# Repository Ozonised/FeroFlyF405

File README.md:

# FeroFlyF405

FeroFlyF405 is an opensource flight controller based on STM32F405 and runs the open source flight controller firmware, [INAV](https://github.com/iNavFlight/inav).

FeroFlyF405 is designed to be an open hardware platform that enthusiasts and developers can study, modify, build, and use in their own projects.

For those interested in the design process, watch the [YouTube](https://youtu.be/mWAzVRxgooY) video.

## Features

* **Microcontroller:** STM32F405
* **IMU:** LSM6DSL 6-axis accelerometer and gyroscope
* **Barometer:** DPS368
* **Firmware:** INAV
* **Motor outputs:** 12 timer-based output channels
* **CAN bus:** For compatible peripherals
* **I2C:** External sensor and peripheral connectivity
* **UARTs:** 3 serial ports
* **PINIO:** 2 programmable GPIO outputs
* **Current sensing:** Dedicated input for an external current sensor

## Sponsor

A special thanks to **[NextPCB](https://www.nextpcb.com/?code=ozonised)** for sponsoring the FeroFlyF405 project and supporting the development of this open-source flight controller.

Their support helped bring the custom PCB design from the screen to the physical board.

Get high quality PCBs for your project at an affordable rate from **[NextPCB](https://www.nextpcb.com/)**.

## Download
Grab the gerbers and kicad file for the latest stable version from the **[release](https://github.com/Ozonised/FeroFlyF405/releases)** tab.

## Connectivity

| Interface      | Quantity | Purpose                                             |
| -------------- | -------: | --------------------------------------------------- |
| Motor outputs  |       12 | ESCs and other compatible timer-based outputs       |
| CAN bus        |        1 | Compatible CAN peripherals                          |
| I2C            |        1 | External sensors and peripherals                    |
| UART           |        3 | Receivers, GPS, telemetry, and other serial devices |
| PINIO          |        2 | User-configurable GPIO outputs                      |
| Current sensor |        1 | External current-sensing module                     |

> **Note:** Motor output capabilities depend on timer allocation, DMA availability, and firmware configuration. Not all outputs necessarily support every ESC protocol.

## Connectors and Pinout

FeroFlyF405 follows the **Pixhawk connector and pinout standard** for its applicable peripheral interfaces and uses **JST-GH series connectors**.

The PINIO and current-sensor connectors are exceptions to this convention.

## Firmware

FeroFlyF405 runs [INAV](https://github.com/iNavFlight/inav), an open-source flight control firmware for multirotor, fixed-wing, and other UAV platforms.

FeroFlyF405 uses a board-specific INAV target to configure its MCU pins, sensors, timers, communication interfaces, and other hardware resources.

Useful links:
* [FeroFlyF405 Target & Binary](https://github.com/Ozonised/FeroFlyF405-INAV-files)
* [INAV source code](https://github.com/iNavFlight/inav)
* [INAV documentation](https://inavflight.github.io/)

## 3D-Printed Enclosure

The FeroFlyF405 enclosure consists of three 3D-printable parts:

* **Enclosure Top** (`FeroFlyF405 Enclosure-Top.stl`) — Upper section of the enclosure.
* **Enclosure Bottom** (`FeroFlyF405 Enclosure-Bottom.stl`) — Lower section of the enclosure.
* **LED Cap** (`FeroFlyF405 Enclosure-Led Cap.stl`) — Cover for the status and power LEDs, designed to be printed using translucent filament to allow the LED light to pass through.

### Printing Recommendations

* **Top and Bottom:** PETG filament is recommended for durability and heat resistance.
* **LED Cap:** Use translucent filament for better LED visibility.
* **Fasteners:** The enclosure uses M3 screws and threaded inserts.

The STL files are provided so you can print and assemble the enclosure yourself.

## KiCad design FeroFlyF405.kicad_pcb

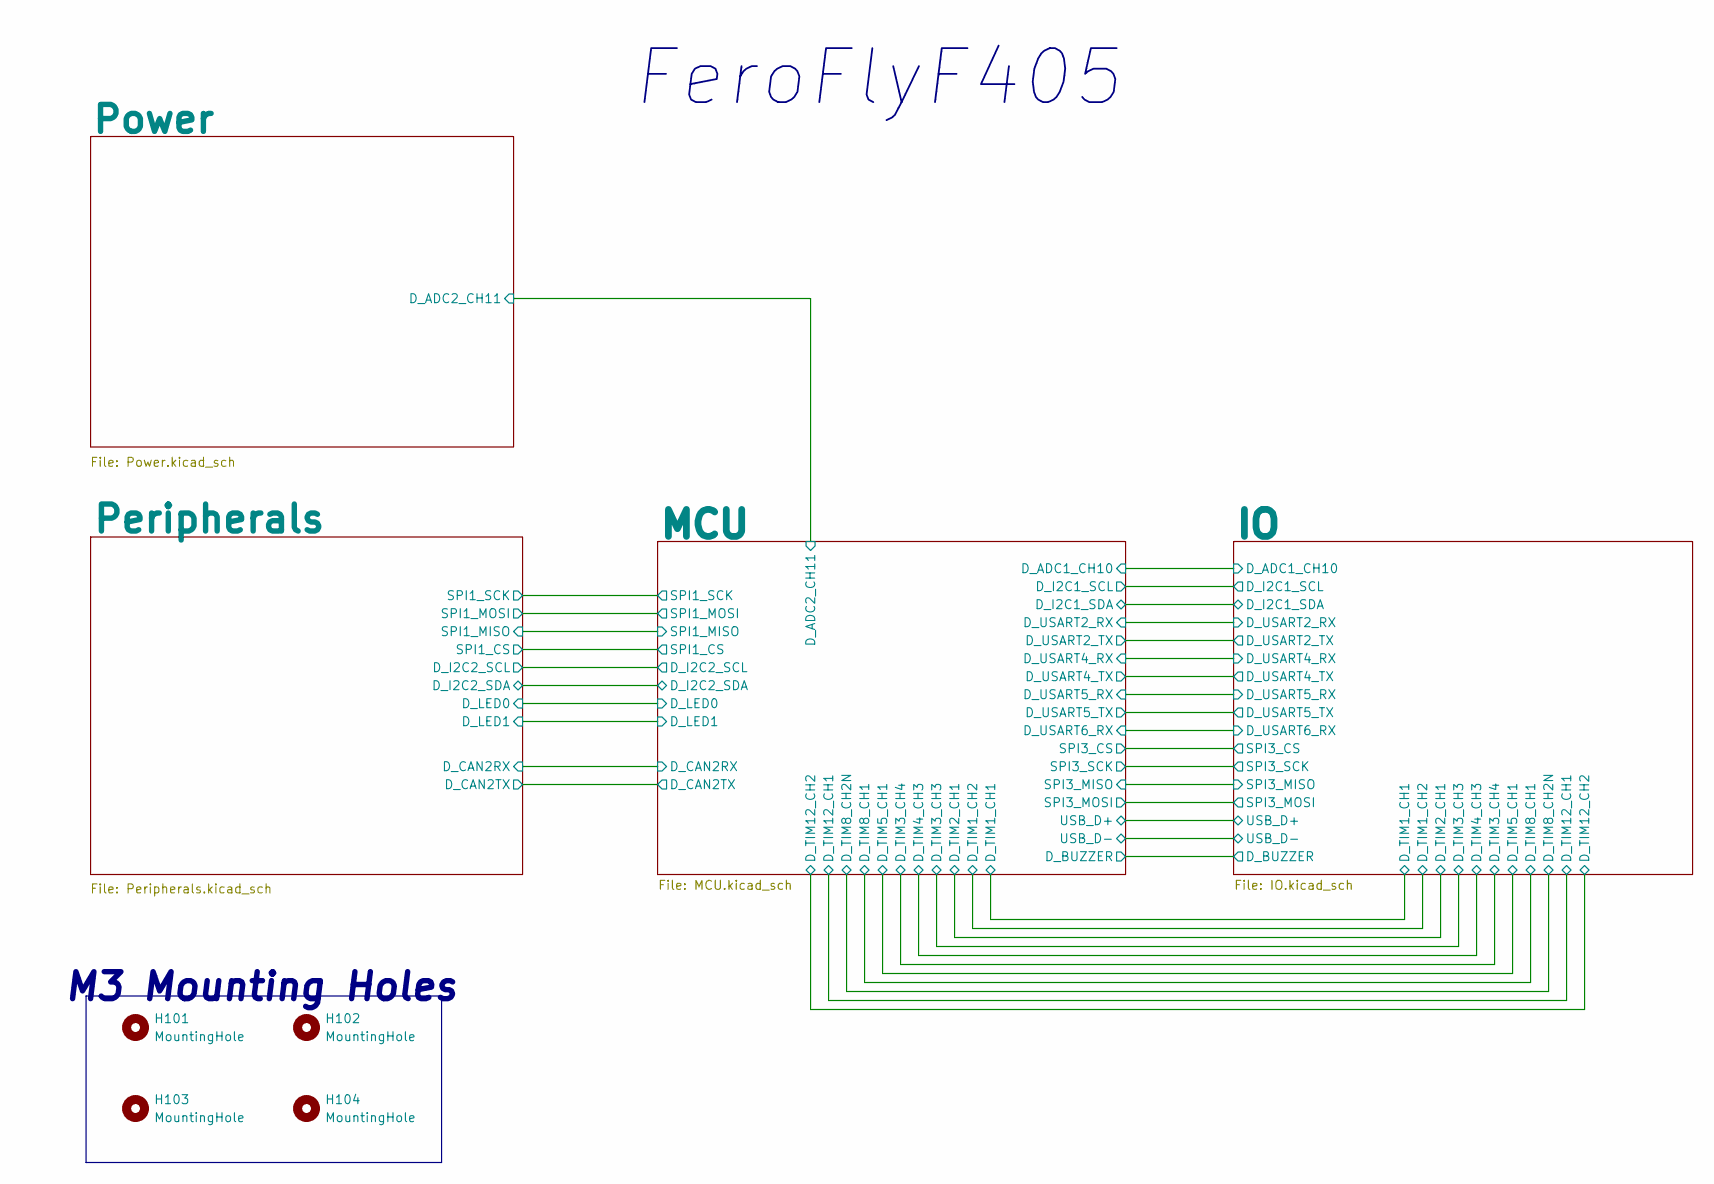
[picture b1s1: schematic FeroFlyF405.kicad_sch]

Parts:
H101, H102, H103, H104: MountingHole; MountingHole_2.2mm_M2

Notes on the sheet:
M3 Mounting Holes
FeroFlyF405

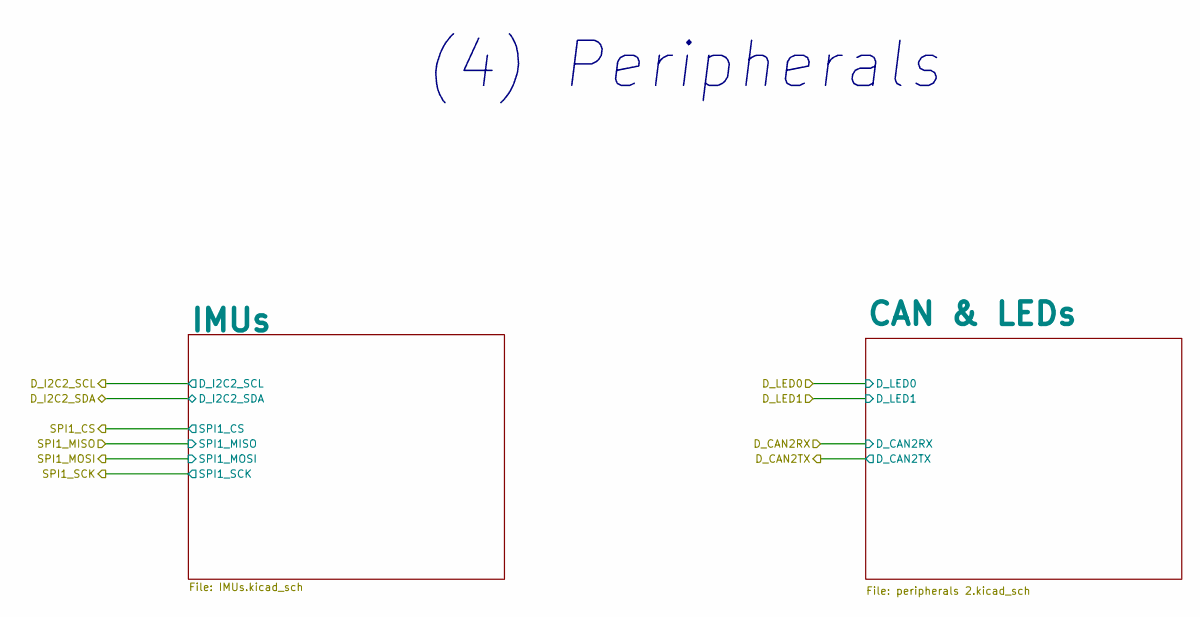
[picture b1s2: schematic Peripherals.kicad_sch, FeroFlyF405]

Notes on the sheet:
(4) Peripherals

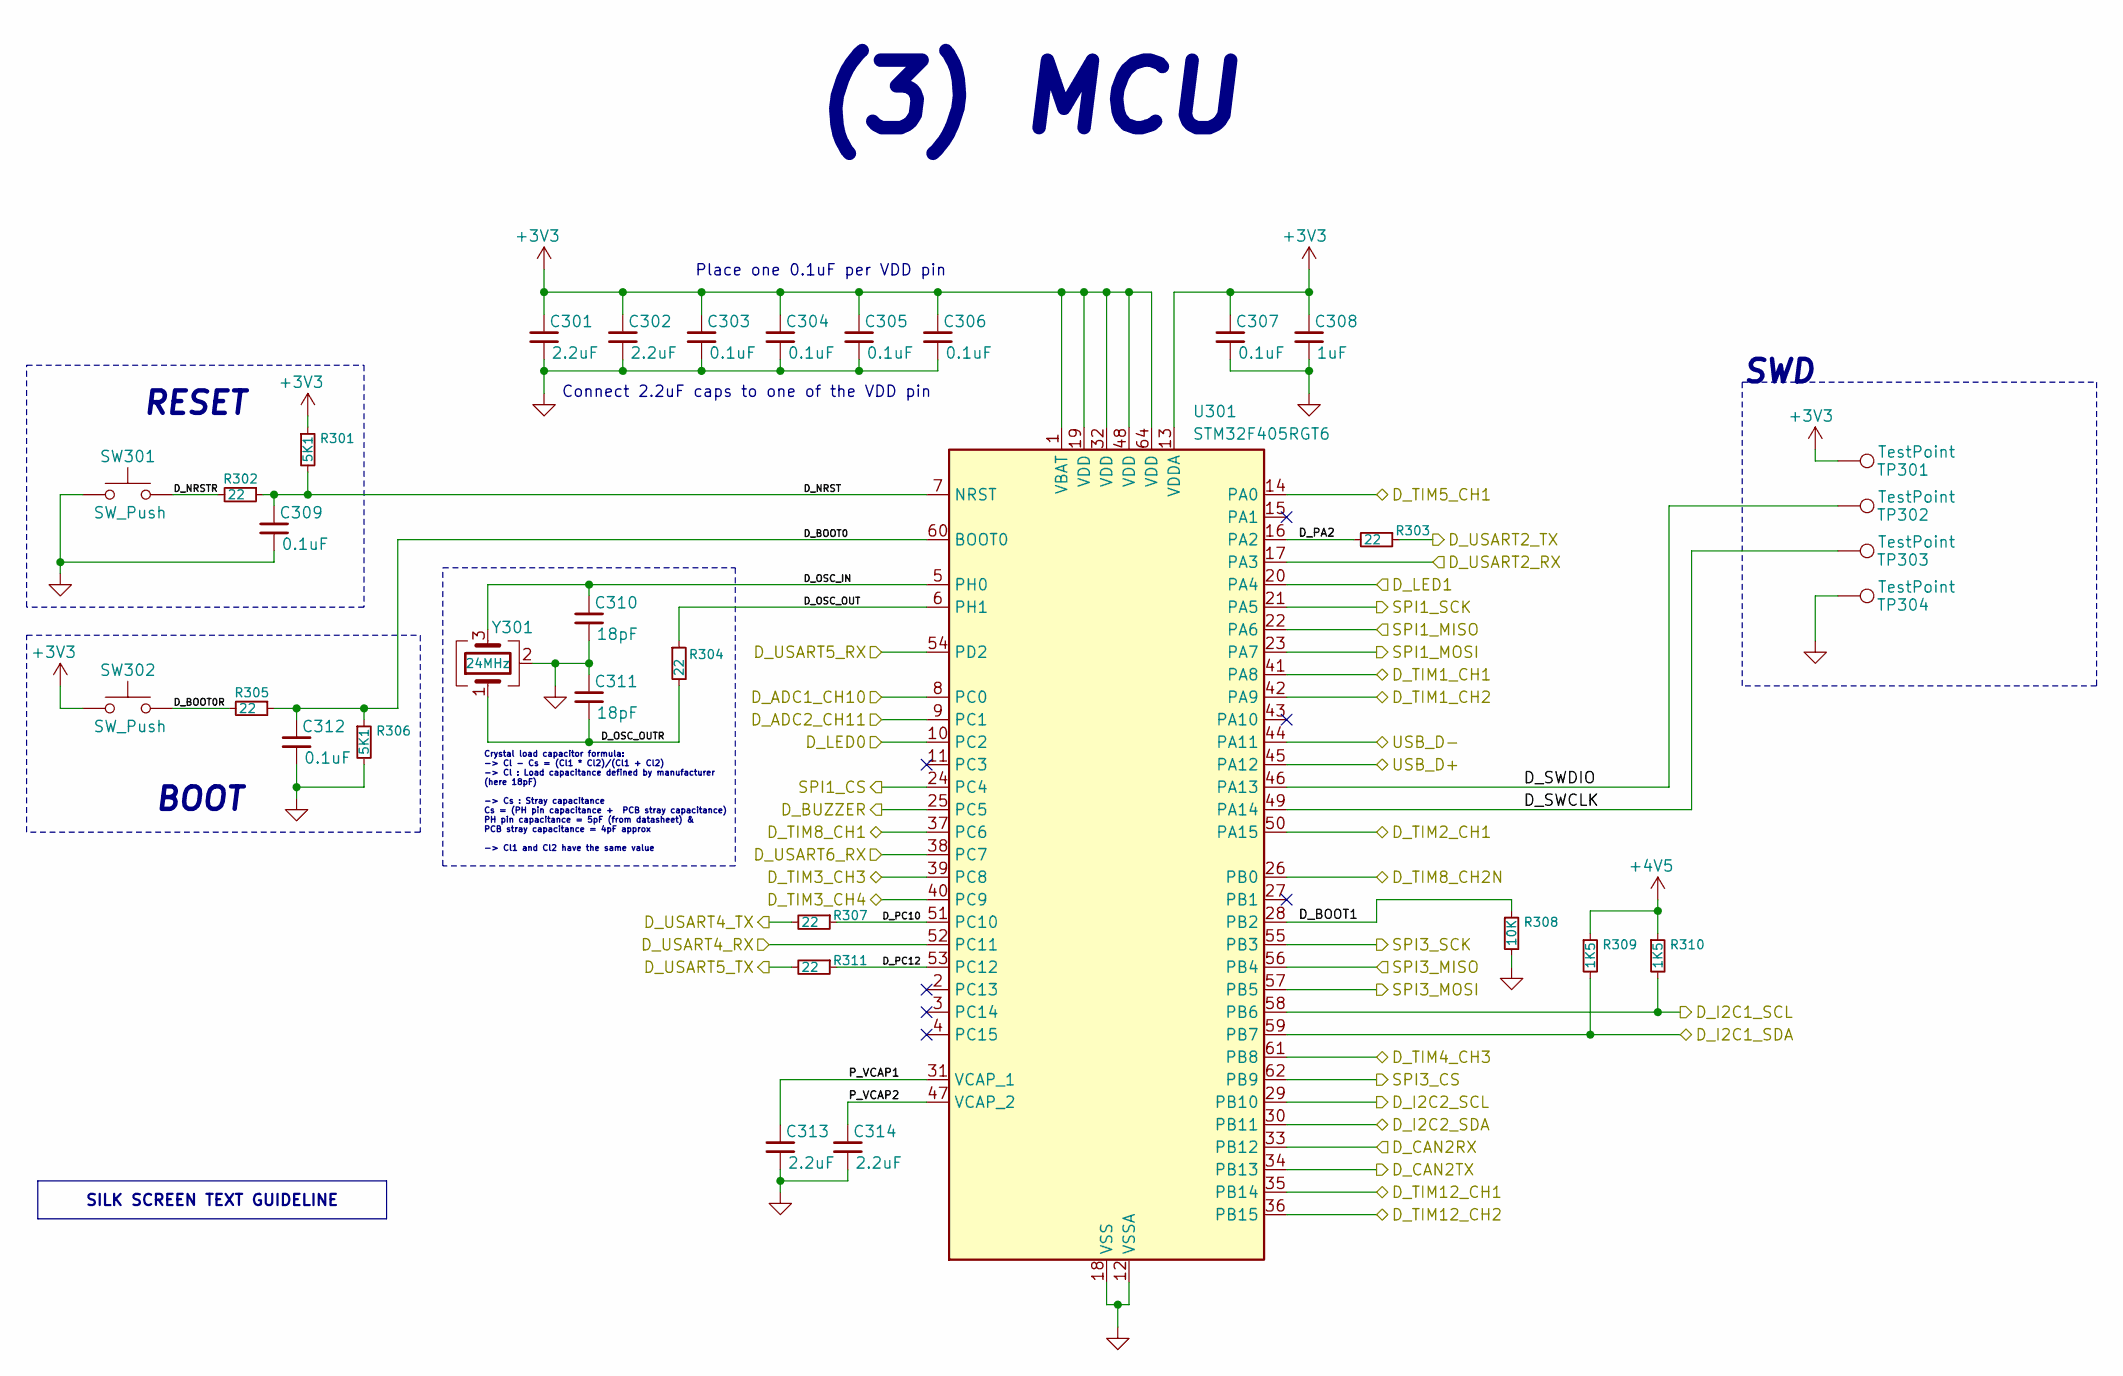
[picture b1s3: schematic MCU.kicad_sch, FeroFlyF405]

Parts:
C301, C302, C313, C314: 2.2uF; C_0805_2012Metric; MPN GCM21BR71C225KA64L
C303, C304, C305, C306, C307, C309, C312: 0.1uF; C_0603_1608Metric_Pad1.08x0.95mm_HandSolder; MPN C1608X5R1H104K080AA
C308: 1uF; C_0603_1608Metric_Pad1.08x0.95mm_HandSolder; MPN C1608X7R1V105K080AC
C310, C311: 18pF; C_0603_1608Metric_Pad1.08x0.95mm_HandSolder; MPN 06035A180JAT4A
R301, R306: 5K1; R_0603_1608Metric_Pad0.98x0.95mm_HandSolder; MPN CR0603-FX-5101ELF
R302, R303, R304, R305, R307, R311: 22; C_0603_1608Metric_Pad1.08x0.95mm_HandSolder; MPN CR0603-FX-22R0ELF
R308: 10K; R_0603_1608Metric_Pad0.98x0.95mm_HandSolder; MPN CR0603-FX-1002ELF
R309, R310: 1K5; R_0603_1608Metric_Pad0.98x0.95mm_HandSolder
SW301, SW302: SW_Push; SW_Push_1P1T_NO_CK_KMR2; MPN RKB2SJM250SMTR LFS
TP301, TP302, TP303, TP304: TestPoint; TestPoint_Pad_D1.0mm
U301: STM32F405RGT6; LQFP-64_10x10mm_P0.5mm; MPN STM32F405RGT6
Y301: 24MHz; Crystal_SMD_3225-4Pin_3.2x2.5mm; MPN ABM8-24.000MHZ-D4Y-T

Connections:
+3V3: C301.1, C302.1, C303.1, C304.1, C305.1, C306.1, C307.1, C308.1, R301.1, SW302.1, TP301.1 (1_1), U301.1 (VBAT), U301.13 (VDDA), U301.19 (VDD), U301.32 (VDD), U301.48 (VDD), U301.64 (VDD); also elsewhere on the board
+4V5: R309.1, R310.1; also elsewhere on the board
/IO/D_ADC1_CH10: U301.8 (PC0); also elsewhere on the board
/IO/D_BUZZER: U301.25 (PC5); also elsewhere on the board
/IO/D_I2C1_SCL: R310.2, U301.58 (PB6); also elsewhere on the board
/IO/D_I2C1_SDA: R309.2, U301.59 (PB7); also elsewhere on the board
/IO/D_TIM1_CH1: U301.41 (PA8); also elsewhere on the board
/IO/D_TIM1_CH2: U301.42 (PA9); also elsewhere on the board
/IO/D_TIM2_CH1: U301.50 (PA15); also elsewhere on the board
/IO/D_TIM3_CH3: U301.39 (PC8); also elsewhere on the board
/IO/D_TIM3_CH4: U301.40 (PC9); also elsewhere on the board
/IO/D_TIM4_CH3: U301.61 (PB8); also elsewhere on the board
/IO/D_TIM5_CH1: U301.14 (PA0); also elsewhere on the board
/IO/D_TIM8_CH1: U301.37 (PC6); also elsewhere on the board
/IO/D_TIM8_CH2N: U301.26 (PB0); also elsewhere on the board
/IO/D_TIM12_CH1: U301.35 (PB14); also elsewhere on the board
/IO/D_TIM12_CH2: U301.36 (PB15); also elsewhere on the board
/IO/D_USART2_RX: U301.17 (PA3); also elsewhere on the board
/IO/D_USART2_TX: R303.1; also elsewhere on the board
/IO/D_USART4_RX: U301.52 (PC11); also elsewhere on the board
/IO/D_USART4_TX: R307.2; also elsewhere on the board
/IO/D_USART5_RX: U301.54 (PD2); also elsewhere on the board
/IO/D_USART5_TX: R311.2; also elsewhere on the board
/IO/D_USART6_RX: U301.38 (PC7); also elsewhere on the board
/IO/SPI3_CS: U301.62 (PB9); also elsewhere on the board
/IO/SPI3_MISO: U301.56 (PB4); also elsewhere on the board
/IO/SPI3_MOSI: U301.57 (PB5); also elsewhere on the board
/IO/SPI3_SCK: U301.55 (PB3); also elsewhere on the board
/IO/USB_D+: U301.45 (PA12); also elsewhere on the board
/IO/USB_D-: U301.44 (PA11); also elsewhere on the board
/MCU/D_ADC2_CH11: U301.9 (PC1); also elsewhere on the board
/MCU/D_BOOT0: C312.1, R305.1, R306.1, U301.60 (BOOT0)
/MCU/D_BOOT0R: R305.2, SW302.2
/MCU/D_BOOT1: R308.1, U301.28 (PB2)
/MCU/D_CAN2RX: U301.33 (PB12); also elsewhere on the board
/MCU/D_CAN2TX: U301.34 (PB13); also elsewhere on the board
/MCU/D_I2C2_SCL: U301.29 (PB10); also elsewhere on the board
/MCU/D_I2C2_SDA: U301.30 (PB11); also elsewhere on the board
/MCU/D_LED0: U301.10 (PC2); also elsewhere on the board
/MCU/D_LED1: U301.20 (PA4); also elsewhere on the board
/MCU/D_NRST: C309.1, R301.2, R302.1, U301.7 (NRST)
/MCU/D_NRSTR: R302.2, SW301.2
/MCU/D_OSC_IN: C310.1, U301.5 (PH0), Y301.3
/MCU/D_OSC_OUT: R304.1, U301.6 (PH1)
/MCU/D_OSC_OUTR: C311.2, R304.2, Y301.1
/MCU/D_PA2: R303.2, U301.16 (PA2)
/MCU/D_PC10: R307.1, U301.51 (PC10)
/MCU/D_PC12: R311.1, U301.53 (PC12)
/MCU/D_SWCLK: TP303.1 (1_1), U301.49 (PA14)
/MCU/D_SWDIO: TP302.1 (1_1), U301.46 (PA13)
/MCU/P_VCAP1: C313.1, U301.31 (VCAP_1)
/MCU/P_VCAP2: C314.1, U301.47 (VCAP_2)
/MCU/SPI1_CS: U301.24 (PC4); also elsewhere on the board
/MCU/SPI1_MISO: U301.22 (PA6); also elsewhere on the board
/MCU/SPI1_MOSI: U301.23 (PA7); also elsewhere on the board
/MCU/SPI1_SCK: U301.21 (PA5); also elsewhere on the board
GND: C301.2, C302.2, C303.2, C304.2, C305.2, C306.2, C307.2, C308.2, C309.2, C310.2, C311.1, C312.2, C313.2, C314.2, R306.2, R308.2, SW301.1, TP304.1 (1_1), U301.12 (VSSA), U301.18 (VSS), U301.63 (VSS), Y301.2 (G), Y301.4 (G); also elsewhere on the board

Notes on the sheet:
RESET
SWD
Place one 0.1uF per VDD pin
Crystal load capacitor formula: -> Cl - Cs = (Cl1 * Cl2)/(Cl1 + Cl2) -> Cl : Load capacitance defined by manufacturer (here 18pF) -> Cs : Stray capacitance Cs = (PH pin capacitance + PCB stray capacitance) PH pin capacitance = 5pF (from datasheet) & PCB stray capacitance = 4pF approx -> Cl1 and Cl2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
(3) MCU
Connect 2.2uF caps to one of the VDD pin
BOOT
SILK SCREEN TEXT GUIDELINE

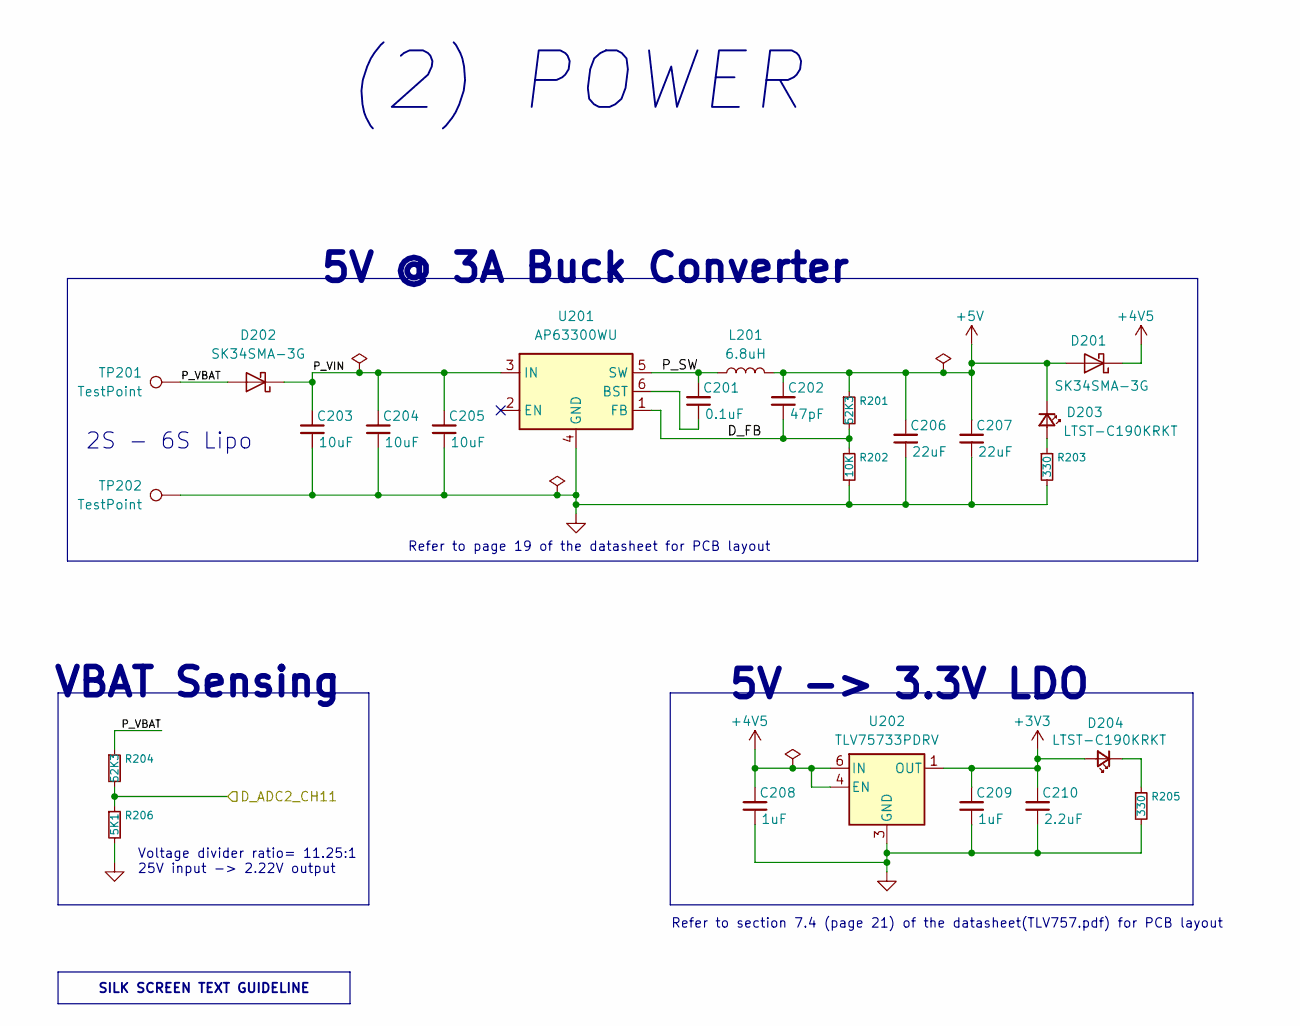
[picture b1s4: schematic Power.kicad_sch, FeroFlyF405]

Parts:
C201: 0.1uF; C_0603_1608Metric_Pad1.08x0.95mm_HandSolder; MPN C1608X5R1H104K080AA
C202: 47pF; C_0603_1608Metric_Pad1.08x0.95mm_HandSolder; MPN CL10C470JB8NNNC
C203, C204, C205: 10uF; C_1210_3225Metric; MPN CL32B106KBJNNNE
C206, C207: 22uF; C_1210_3225Metric; MPN C3225X5R1C226M250AA
C208, C209: 1uF; C_0603_1608Metric_Pad1.08x0.95mm_HandSolder; MPN C1608X7R1V105K080AC
C210: 2.2uF; C_0805_2012Metric; MPN GCM21BR71C225KA64L
D201, D202: SK34SMA-3G; D_SMA; MPN SK34SMA-3G
D203, D204: LTST-C190KRKT; LED_0603_1608Metric_Pad1.05x0.95mm_HandSolder; MPN LTST-C190KRKT
L201: 6.8uH; L_TDK_VLS6045EX_VLS6045AF; MPN VLS6045EX-6R8M
R201, R204: 52K3; C_0603_1608Metric_Pad1.08x0.95mm_HandSolder; MPN CR0603-FX-5232ELF
R202: 10K; R_0603_1608Metric_Pad0.98x0.95mm_HandSolder; MPN CR0603-FX-1002ELF
R203, R205: 330; R_0603_1608Metric_Pad0.98x0.95mm_HandSolder; MPN CR0603-FX-3300ELF
R206: 5K1; R_0603_1608Metric_Pad0.98x0.95mm_HandSolder; MPN CR0603-FX-5101ELF
TP201, TP202: TestPoint; TestPoint_Pad_2.0x2.0mm
U201: AP63300WU; TSOT-23-6; MPN AP63300WU
U202: TLV75733PDRV; WSON-6-1EP_2x2mm_P0.65mm_EP1x1.6mm; MPN TLV75733PDRVR

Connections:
+3V3: C209.1, C210.1, D204.2 (A), U202.1 (OUT); also elsewhere on the board
+4V5: C208.1, D201.1 (K), U202.4 (EN), U202.6 (IN); also elsewhere on the board
+5V: C202.1, C206.1, C207.1, D201.2 (A), D203.1 (K), L201.2, R201.1; also elsewhere on the board
/MCU/D_ADC2_CH11: R204.2, R206.1; also elsewhere on the board
/Power/D_FB: C202.2, R201.2, R202.1, U201.1 (FB)
/Power/P_SW: C201.1, L201.1, U201.5 (SW)
/Power/P_VBAT: D202.2 (A), R204.1, TP201.1 (1_1)
/Power/P_VIN: C203.1, C204.1, C205.1, D202.1 (K), U201.3 (IN)
GND: C203.2, C204.2, C205.2, C206.2, C207.2, C208.2, C209.2, C210.2, R202.2, R203.2, R205.2, R206.2, TP202.1 (1_1), U201.4 (GND), U202.3 (GND), U202.7 (GND); also elsewhere on the board
unnamed: D203.2 (A), R203.1
unnamed: D204.1 (K), R205.1
unnamed: C201.2, U201.6 (BST)

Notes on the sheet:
Refer to page 19 of the datasheet for PCB layout
5V -> 3.3V LDO
5V @ 3A Buck Converter
(2) POWER
Refer to section 7.4 (page 21) of the datasheet(TLV757.pdf) for PCB layout
Voltage divider ratio= 11.25:1 25V input -> 2.22V output
VBAT Sensing
2S - 6S Lipo
SILK SCREEN TEXT GUIDELINE

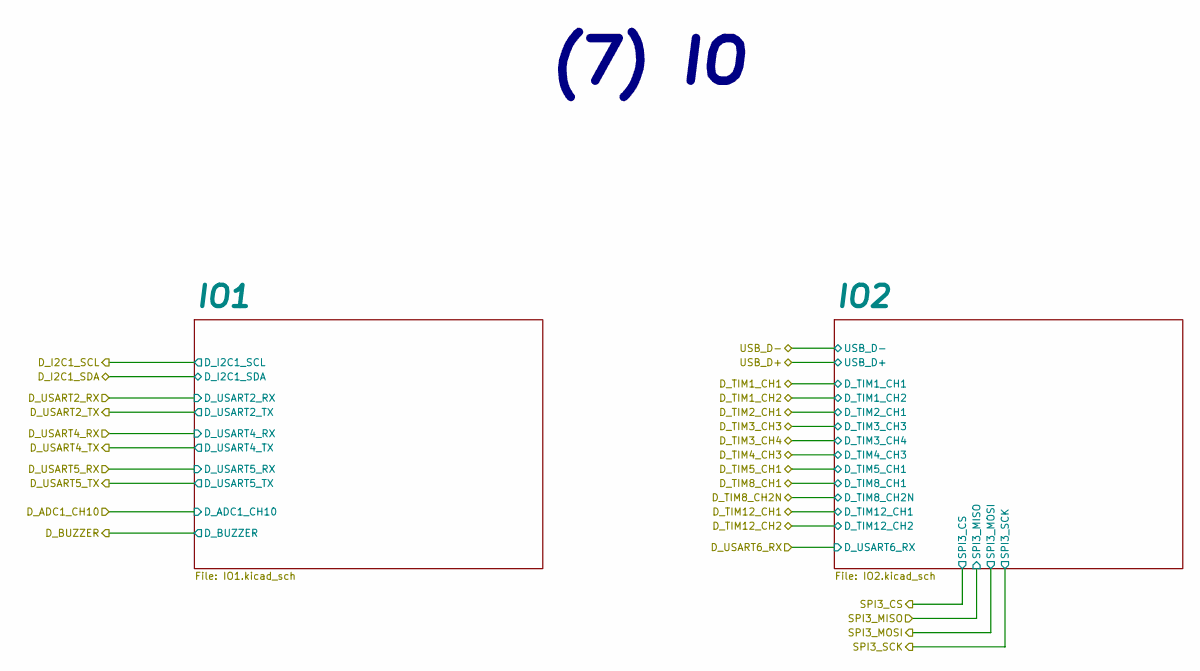
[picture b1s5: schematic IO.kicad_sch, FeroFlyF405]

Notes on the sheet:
(7) IO

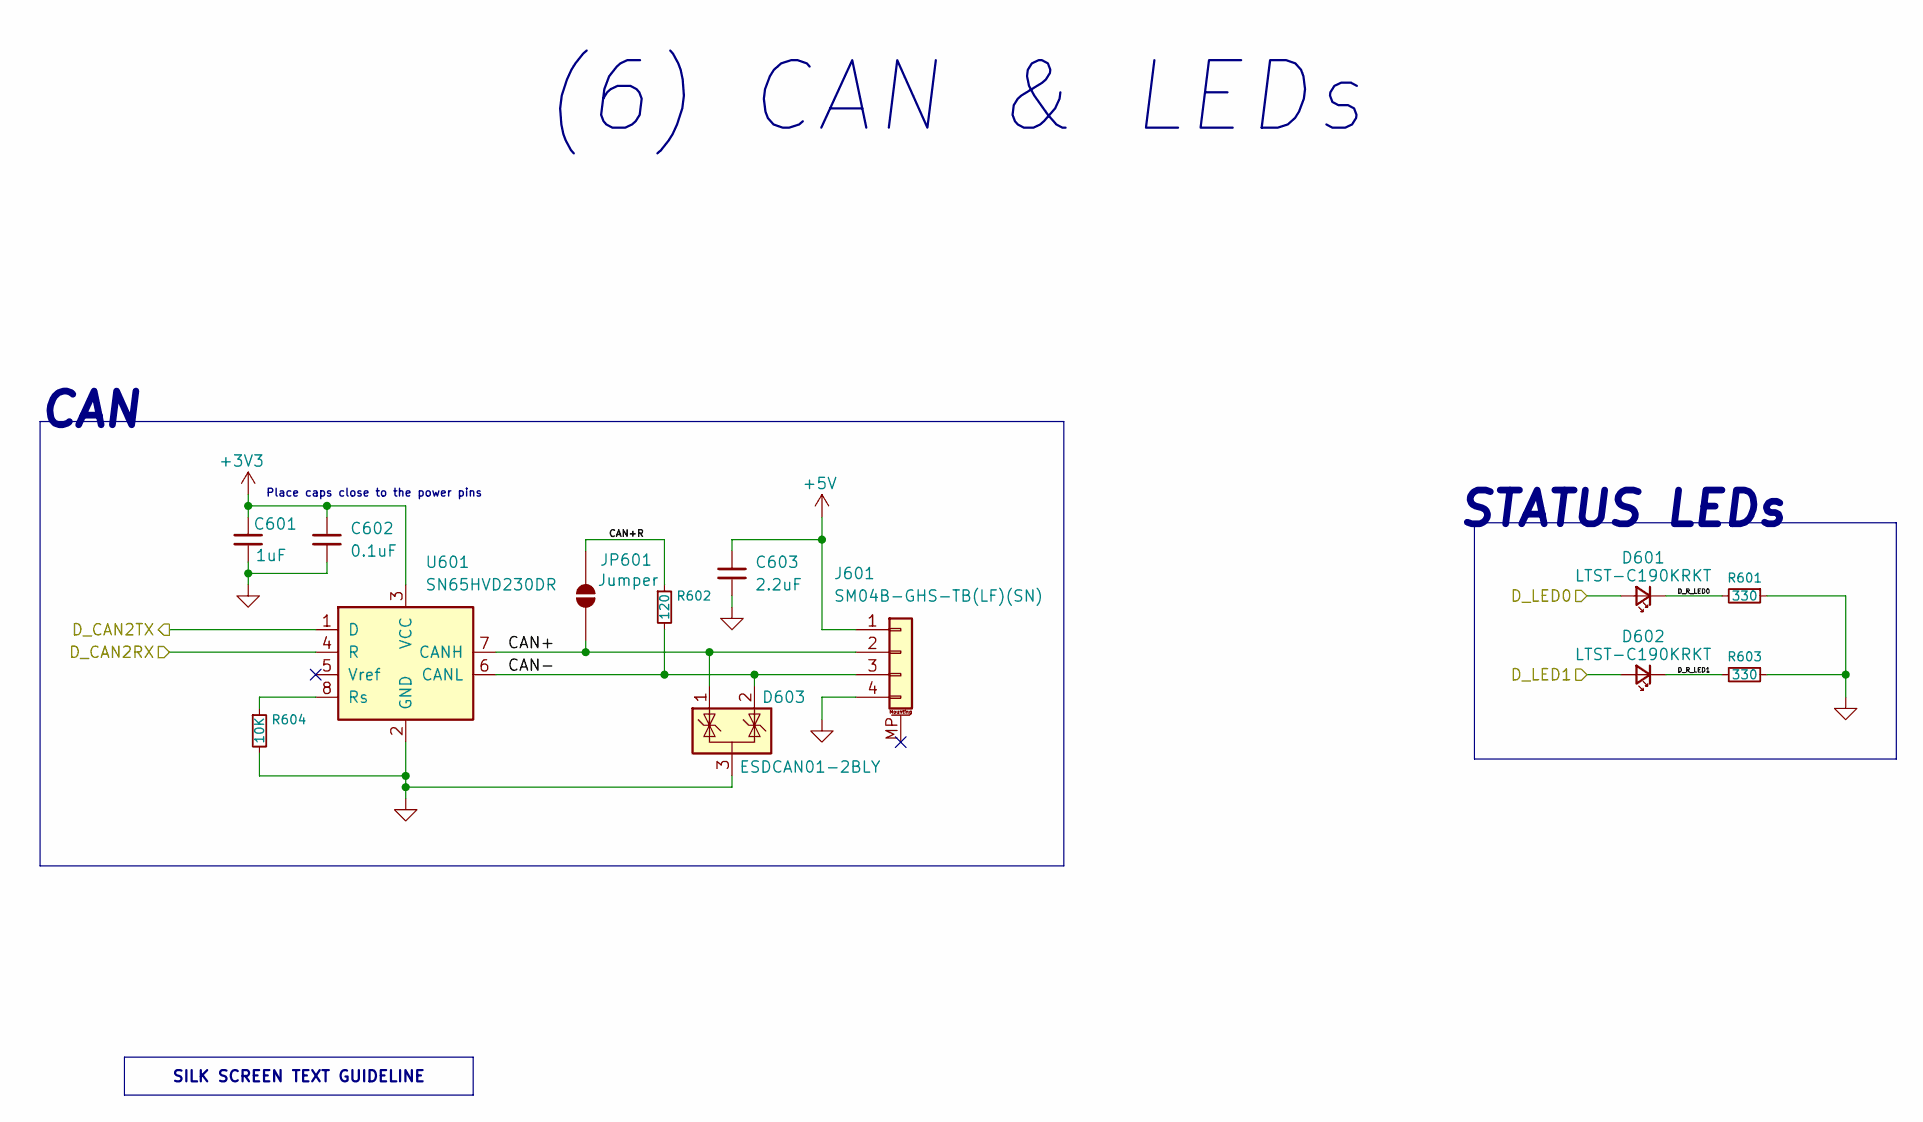
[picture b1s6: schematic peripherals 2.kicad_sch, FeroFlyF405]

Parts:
C601: 1uF; C_0603_1608Metric_Pad1.08x0.95mm_HandSolder; MPN C1608X7R1V105K080AC
C602: 0.1uF; C_0603_1608Metric_Pad1.08x0.95mm_HandSolder; MPN C1608X5R1H104K080AA
C603: 2.2uF; C_0805_2012Metric; MPN GCM21BR71C225KA64L
D601, D602: LTST-C190KRKT; LED_0603_1608Metric_Pad1.05x0.95mm_HandSolder; MPN LTST-C190KRKT
D603: ESDCAN01-2BLY; SOT-23; MPN ESDCAN01-2BLY
J601: SM04B-GHS-TB(LF)(SN); JST_GH_SM04B-GHS-TB_1x04-1MP_P1.25mm_Horizontal; MPN SM04B-GHS-TB(LF)(SN)
JP601: Jumper; SolderJumper-2_P1.3mm_Open_TrianglePad1.0x1.5mm
R601, R603: 330; R_0603_1608Metric_Pad0.98x0.95mm_HandSolder; MPN CR0603-FX-3300ELF
R602: 120; R_1206_3216Metric_Pad1.30x1.75mm_HandSolder; MPN CR1206-FX-1200ELF
R604: 10K; R_0603_1608Metric_Pad0.98x0.95mm_HandSolder; MPN CR0603-FX-1002ELF
U601: SN65HVD230DR; SOIC-8_3.9x4.9mm_P1.27mm; MPN SN65HVD230DR

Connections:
+3V3: C601.1, C602.1, U601.3 (VCC); also elsewhere on the board
+5V: C603.1, J601.1; also elsewhere on the board
/MCU/D_CAN2RX: U601.4 (R); also elsewhere on the board
/MCU/D_CAN2TX: U601.1 (D); also elsewhere on the board
/MCU/D_LED0: D601.2 (A); also elsewhere on the board
/MCU/D_LED1: D602.2 (A); also elsewhere on the board
/Peripherals/CAN & LEDs/CAN+: D603.1 (K), J601.2, JP601.1 (A), U601.7 (CANH)
/Peripherals/CAN & LEDs/CAN+R: JP601.2 (B), R602.1
/Peripherals/CAN & LEDs/CAN-: D603.2 (K), J601.3, R602.2, U601.6 (CANL)
/Peripherals/CAN & LEDs/D_R_LED0: D601.1 (K), R601.2
/Peripherals/CAN & LEDs/D_R_LED1: D602.1 (K), R603.2
GND: C601.2, C602.2, C603.2, D603.3 (A), J601.4, R601.1, R603.1, R604.2, U601.2 (GND); also elsewhere on the board
unnamed: R604.1, U601.8 (Rs)

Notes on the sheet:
(6) CAN & LEDs
STATUS LEDs
Place caps close to the power pins
CAN
SILK SCREEN TEXT GUIDELINE

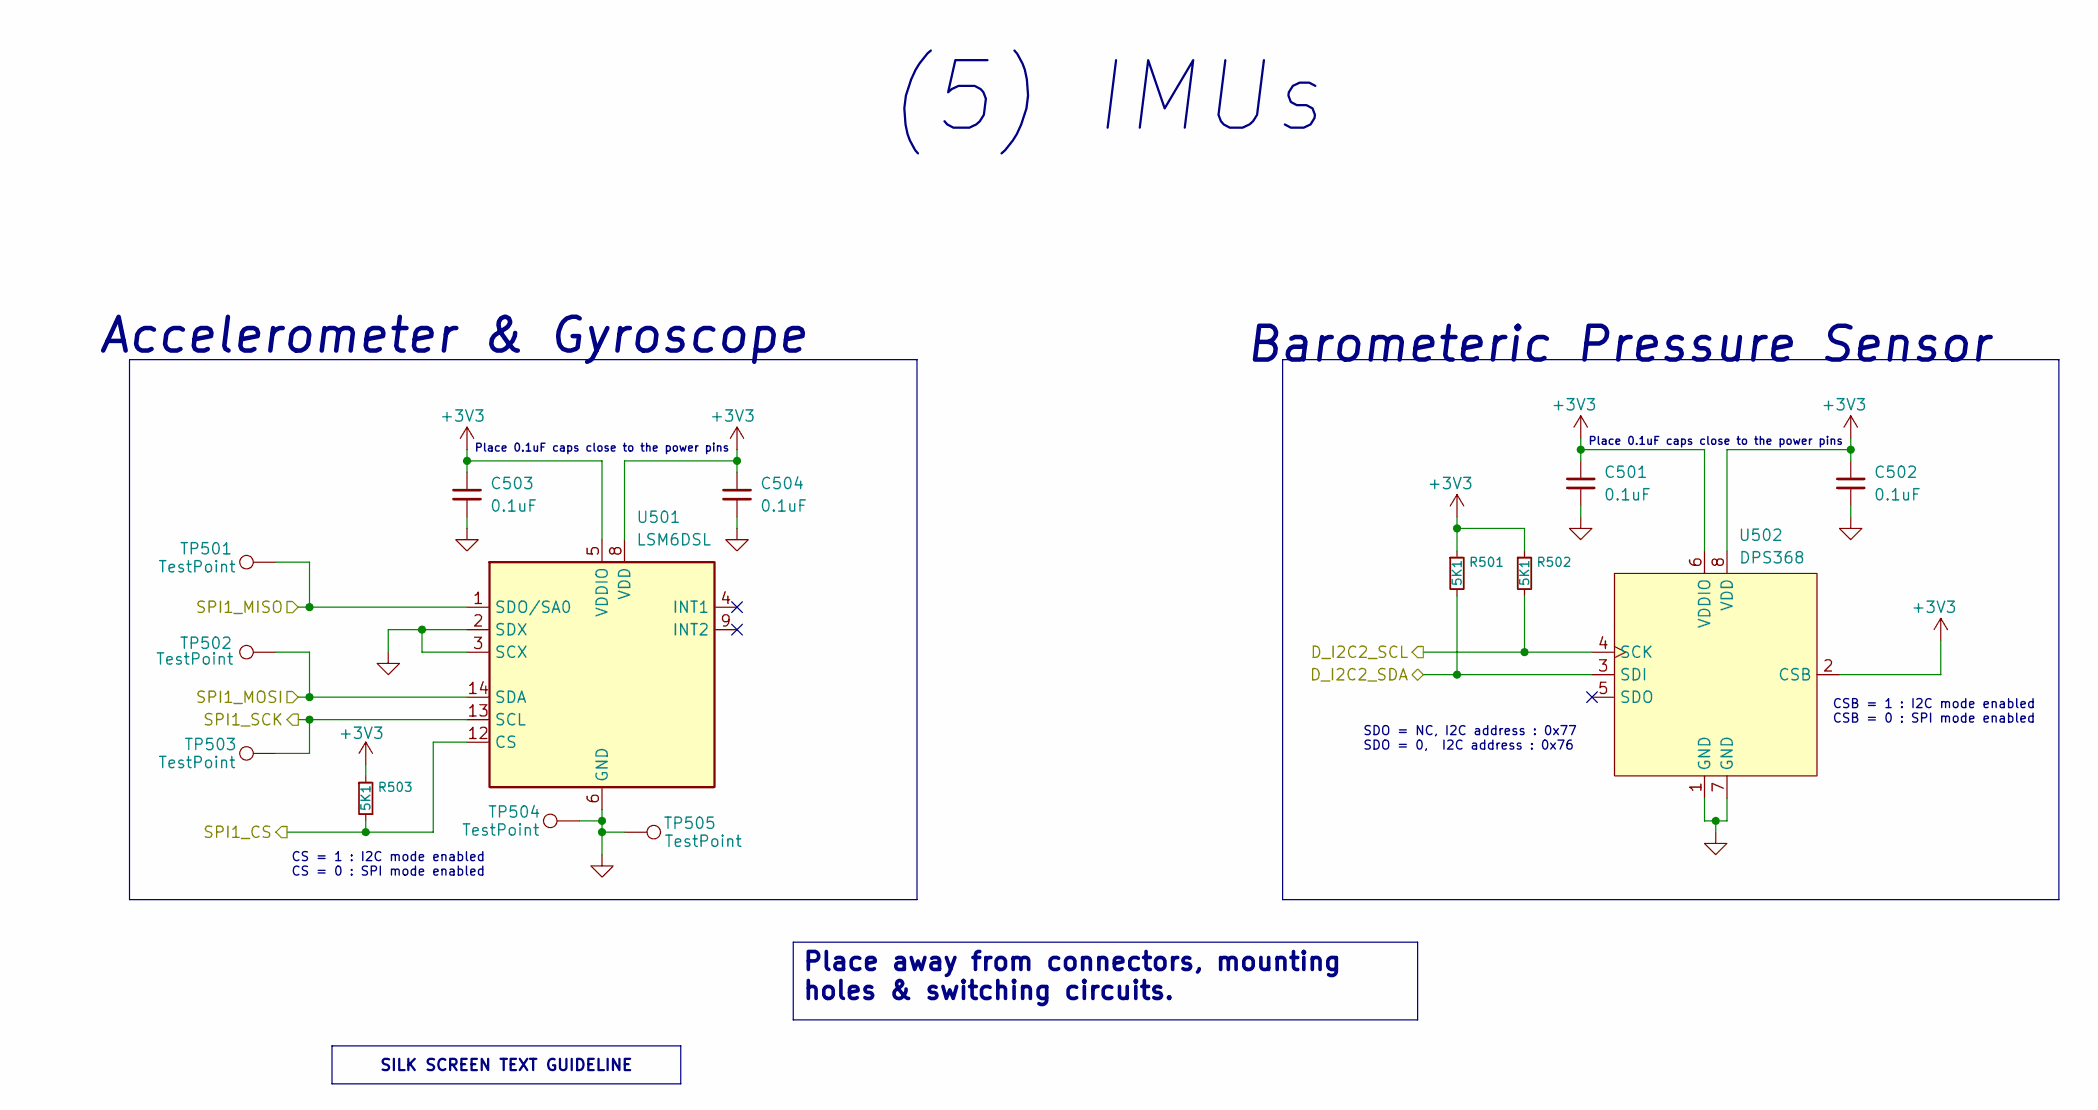
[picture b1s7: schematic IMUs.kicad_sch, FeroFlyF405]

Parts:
C501, C502, C503, C504: 0.1uF; C_0603_1608Metric_Pad1.08x0.95mm_HandSolder; MPN C1608X5R1H104K080AA
R501, R502, R503: 5K1; R_0603_1608Metric_Pad0.98x0.95mm_HandSolder; MPN CR0603-FX-5101ELF
TP501, TP502, TP503, TP504, TP505: TestPoint; TestPoint_Pad_D1.0mm
U501: LSM6DSL; LGA-14_3x2.5mm_P0.5mm_LayoutBorder3x4y; MPN LSM6DSL
U502: DPS368; Bosch_LGA-8_2x2.5mm_P0.65mm_ClockwisePinNumbering; MPN DPS368

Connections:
+3V3: C501.1, C502.1, C503.1, C504.1, R501.1, R502.1, R503.1, U501.5 (VDDIO), U501.8 (VDD), U502.2 (CSB), U502.6 (VDDIO), U502.8 (VDD); also elsewhere on the board
/MCU/D_I2C2_SCL: R502.2, U502.4 (SCK); also elsewhere on the board
/MCU/D_I2C2_SDA: R501.2, U502.3 (SDI); also elsewhere on the board
/MCU/SPI1_CS: R503.2, U501.12 (CS); also elsewhere on the board
/MCU/SPI1_MISO: TP501.1 (1_1), U501.1 (SDO/SA0); also elsewhere on the board
/MCU/SPI1_MOSI: TP502.1 (1_1), U501.14 (SDA); also elsewhere on the board
/MCU/SPI1_SCK: TP503.1 (1_1), U501.13 (SCL); also elsewhere on the board
GND: C501.2, C502.2, C503.2, C504.2, TP504.1 (1_1), TP505.1 (1_1), U501.2 (SDX), U501.3 (SCX), U501.6 (GND), U501.7 (GND), U502.1 (GND), U502.7 (GND); also elsewhere on the board

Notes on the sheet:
SDO = NC, I2C address : 0x77 SDO = 0, I2C address : 0x76
CSB = 1 : I2C mode enabled CSB = 0 : SPI mode enabled
Accelerometer & Gyroscope
(5) IMUs
CS = 1 : I2C mode enabled CS = 0 : SPI mode enabled
Place 0.1uF caps close to the power pins
Barometeric Pressure Sensor
SILK SCREEN TEXT GUIDELINE
Place away from connectors, mounting holes & switching circuits.

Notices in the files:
FeroFlyF405.kicad_pcb:
LICENSE: CERN-OHL-S-2.0
